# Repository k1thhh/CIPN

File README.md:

# 🩺 Chemo Comfort — AI-Based Wearable for Early Detection of CIPN

<p align="center">

**Embedded Healthcare | TinyML | ESP32 | Biomedical Sensing | Edge AI**

</p>

---

## 📌 Overview

**Chemo Comfort** is a portable, low-cost embedded diagnostic prototype designed for the **early, objective screening of Chemotherapy-Induced Peripheral Neuropathy (CIPN)**.

The system combines three complementary assessment methods:

* A simplified **EORTC QLQ-CIPN20 questionnaire**
* **Vibration Perception Threshold (VPT)** testing
* **Cold-temperature perception testing**

The extracted features are processed directly on an **ESP32-WROOM** using a quantized **TensorFlow Lite Micro neural network**, allowing the device to classify CIPN risk without relying on cloud connectivity.

The system produces one of three risk categories:

```text
Normal
Moderate
Severe
```

All processing is performed locally on the device, providing a privacy-preserving architecture suitable for potential home or outpatient applications.

> ⚠️ **Important:** Chemo Comfort is an academic/research prototype and is **not a certified medical device**. It is not intended for clinical diagnosis without further validation.

---

# 🩺 About Chemotherapy-Induced Peripheral Neuropathy

**Chemotherapy-Induced Peripheral Neuropathy (CIPN)** is a common adverse effect associated with several chemotherapy agents, including taxanes, platinum compounds, and vinca alkaloids.

Conventional assessment can involve:

* Patient-reported questionnaires
* Clinical grading scales
* Nerve conduction studies
* Quantitative sensory testing

The project aims to combine subjective patient-reported information with quantitative sensory measurements in a single portable embedded system.

---

# 🎯 Project Objectives

The primary objectives are:

1. Develop a portable embedded system for CIPN screening.
2. Collect patient-reported sensory, motor, and autonomic symptoms.
3. Measure vibration perception thresholds.
4. Measure cold-temperature perception.
5. Combine multiple sensory indicators into a unified feature vector.
6. Perform feature normalization directly on the ESP32.
7. Deploy a quantized TinyML model on-device.
8. Classify CIPN risk into Normal, Moderate, or Severe categories.
9. Display the classification locally using an OLED.
10. Eliminate the requirement for cloud-based inference.
11. Develop a low-cost prototype suitable for further research and validation.

---

# 🏗️ System Architecture

The system combines three input modules before performing edge inference.

```text id="4u9b3c"
┌─────────────────────┐
│   Questionnaire     │
│   OLED + Buttons    │
└──────────┬──────────┘
           │
           │
┌──────────▼──────────┐
│   Vibration Test    │
│    DRV2605L ×2      │
└──────────┬──────────┘
           │
           │
┌──────────▼──────────┐
│   Thermal Test      │
│ Peltier + Temp      │
│      Sensor         │
└──────────┬──────────┘
           │
           ▼
┌─────────────────────────┐
│       ESP32-WROOM       │
│                         │
│ Feature Normalization   │
│ Mean / Std Scaling      │
└────────────┬────────────┘
             │
             ▼
┌─────────────────────────┐
│   TFLite Micro Model    │
│     INT8 Quantized      │
│                         │
│ Dense(16, ReLU)         │
│        ↓                │
│ Dense(1, Sigmoid)       │
└────────────┬────────────┘
             │
             ▼
┌─────────────────────────┐
│      OLED Display       │
│ Normal / Moderate /     │
│ Severe                  │
└─────────────────────────┘
```

The five model features are:

```text id="e5q8kj"
VPT
Cold Temperature
CIPN20 Sensory
CIPN20 Motor
CIPN20 Autonomic
```

These features are normalized on-device using the same preprocessing parameters used during model development.

---

# 🔬 Assessment Modules

## 1️⃣ Questionnaire Module

The device presents a simplified **EORTC QLQ-CIPN20-based questionnaire** through the OLED display.

Five push buttons are used for interaction:

* Four questionnaire response buttons
* One reset/response button

The questionnaire contributes sensory, motor, and autonomic symptom features to the final model input.

---

# 2️⃣ Vibration Perception Threshold Test

The VPT test evaluates the user's ability to perceive controlled vibration stimuli.

The system uses **DRV2605L haptic drivers** to generate controlled vibration.

```text id="z3q1n0"
ESP32
  │
  ▼
DRV2605L
  │
  ▼
Increasing Vibration
  │
  ▼
Patient Perception
  │
  ▼
Button Response
  │
  ▼
VPT Threshold
```

The vibration intensity is progressively increased until the patient indicates that the vibration can be perceived.

The project reports VPT threshold trends of approximately:

```text id="kr9n5a"
Non-CIPN → Median 7–8
CIPN     → Median 17–18
```

---

# 3️⃣ Thermal Perception Test

The thermal test evaluates cold-temperature perception.

The system uses:

* TEC1-12706 Peltier module
* DS18B20 / TMP117 temperature sensor
* MOSFET H-bridge

The Peltier module changes the temperature of a contact surface while the temperature sensor continuously measures the resulting temperature.

```text id="n6l4yw"
ESP32
  │
  ▼
MOSFET H-Bridge
  │
  ▼
Peltier Module
  │
  ▼
Cooling Surface
  │
  ▼
Patient Perception
  │
  ▼
Cold Detection Threshold
```

The project reports cold-detection temperatures around:

```text id="d7b5ai"
30.0 – 30.7 °C
```

---

# 🧠 Feature Extraction

The three assessment modules produce the five model inputs:

| Feature            | Source                    |
| ------------------ | ------------------------- |
| `vpt`              | Vibration perception test |
| `cold_temp`        | Thermal perception test   |
| `cipn20_sensory`   | Questionnaire             |
| `cipn20_motor`     | Questionnaire             |
| `cipn20_autonomic` | Questionnaire             |

The complete feature vector is therefore:

```text id="j4bdl7"
[vpt,
 cold_temp,
 cipn20_sensory,
 cipn20_motor,
 cipn20_autonomic]
```

The preprocessing parameters are stored in:

```text id="4px0ck"
ml/model/preproc_params.json
```

and mirrored as constants in the firmware.

---

# 🤖 Machine Learning Pipeline

The machine-learning pipeline was developed using **Python, TensorFlow, and Google Colab**.

```text id="m2h52d"
Clinical / Synthetic Data
          │
          ▼
    Dataset Synthesis
          │
          ▼
     Preprocessing
          │
    ┌─────┴─────┐
    ▼           ▼
Imputation   Standardization
    │           │
    └─────┬─────┘
          ▼
       MLP Model
          │
          ▼
      Training
          │
          ▼
    TensorFlow Lite
          │
          ▼
     INT8 Quantization
          │
          ▼
       model.h
          │
          ▼
       ESP32
```

---

# 📊 Dataset Development

Because a public dataset combining quantitative sensory measurements with CIPN-20 scores was not available for the project's requirements, a **synthetic dataset** was generated.

The dataset was constructed using statistical patterns reported in published literature, with controlled mean and standard-deviation shifts between CIPN and non-CIPN classes.

This approach allowed the embedded ML pipeline to be developed and tested while recognizing that clinical validation with real patient data remains necessary.

---

# ⚙️ Data Preprocessing

The ML pipeline applies two major preprocessing operations.

## Median Imputation

Missing values are handled using:

```text id="u8scnd"
SimpleImputer
      ↓
Median Imputation
```

---

## Feature Standardization

The features are standardized using:

```text id="qzqu2m"
StandardScaler
```

The resulting mean and scaling parameters are saved in:

```text id="5w9f84"
preproc_params.json
```

The same preprocessing parameters are embedded into the ESP32 firmware to maintain consistency between training and inference.

---

# 🧠 Neural Network Architecture

The project uses a compact **two-layer Multilayer Perceptron (MLP)**.

```text id="3f53f5"
5 Input Features
       │
       ▼
┌──────────────────┐
│ Dense Layer      │
│ 16 Neurons       │
│ ReLU Activation  │
└────────┬─────────┘
         │
         ▼
┌──────────────────┐
│ Dense Layer      │
│ 1 Neuron         │
│ Sigmoid           │
└────────┬─────────┘
         │
         ▼
    CIPN Risk Score
```

The model was trained for:

```text id="4c3vqt"
Epochs      = 30
Optimizer   = Adam
Learning Rate = 0.001
Train/Test  = 85:15
```

---

# 📦 TensorFlow Lite Conversion

After training, the model is converted into an embedded-friendly representation.

```text id="m2trm8"
Keras Model
    ↓
TensorFlow Lite
    ↓
INT8 Post-Training Quantization
    ↓
C Array
    ↓
model.h
    ↓
ESP32 Firmware
```

The resulting `model.h` file contains the TensorFlow Lite model as a C byte array that can be compiled directly into the ESP32 firmware.

---

# ⚡ On-Device TinyML

One of the major features of Chemo Comfort is that inference occurs **directly on the ESP32**.

```text id="d0c4au"
Patient Data
     ↓
Feature Extraction
     ↓
Normalization
     ↓
INT8 TinyML Model
     ↓
Risk Classification
     ↓
OLED
```

No cloud server is required for inference.

This provides:

* Lower dependency on internet connectivity
* Local processing
* Improved privacy
* Potentially faster response
* Portable operation

The firmware executes the model using a **32 KB tensor arena**.

---

# 🖥️ OLED User Interface

A **0.96-inch 128×64 I²C OLED** provides the user interface.

It displays:

* Questionnaire prompts
* Progress
* Test information
* Final CIPN risk classification

The final classification is displayed as:

```text id="5qv8aq"
┌──────────────────┐
│   CIPN RESULT    │
│                  │
│     NORMAL       │
│       OR         │
│    MODERATE      │
│       OR         │
│     SEVERE       │
└──────────────────┘
```

---

# 💻 Firmware Architecture

The main firmware is:

```text id="3myq5u"
firmware/cipn_tinyml.ino
```

It integrates the complete embedded workflow.

The firmware handles:

* OLED interface
* Questionnaire flow
* Button debouncing
* VPT testing
* Thermal testing
* Feature normalization
* TinyML inference
* Risk classification
* Result display

---

# 🔌 Hardware Architecture

| Component              | Function                           |
| ---------------------- | ---------------------------------- |
| **ESP32-WROOM**        | Main controller + TinyML inference |
| **DRV2605L ×2**        | Vibration stimulus generation      |
| **TEC1-12706 Peltier** | Thermal stimulus                   |
| **DS18B20 / TMP117**   | Temperature sensing                |
| **MOSFET H-Bridge**    | Bidirectional Peltier control      |
| **MT3608**             | Boost conversion                   |
| **0.96" OLED**         | User interface                     |
| **5 Push Buttons**     | Questionnaire and test interaction |

The ESP32-WROOM uses a dual-core Xtensa LX6 architecture operating at up to 240 MHz with 520 KB SRAM.

---

# 💰 Cost Analysis

The prototype has an estimated total component cost of approximately:

## **₹1,710**

| Component          | Qty | Unit Cost |        Total |
| ------------------ | --: | --------: | -----------: |
| ESP32-WROOM        |   1 |      ₹400 |         ₹400 |
| DRV2605L           |   2 |      ₹180 |         ₹360 |
| Peltier Module     |   1 |      ₹200 |         ₹200 |
| DS18B20/TMP117     |   1 |      ₹120 |         ₹120 |
| MT3608             |   1 |       ₹80 |          ₹80 |
| OLED               |   1 |      ₹150 |         ₹150 |
| Push Buttons       |   5 |       ₹10 |          ₹50 |
| MOSFET H-Bridge    |   1 |      ₹100 |         ₹100 |
| Power Supply / USB |   1 |      ₹100 |         ₹100 |
| Miscellaneous      |   — |         — |         ₹150 |
| **Total**          |     |           | **≈ ₹1,710** |

---

# 📁 Repository Structure

```text id="y5x4b9"
ChemoComfort-CIPN-Wearable/
│
├── README.md
│
├── docs/
│   └── Chemo_Comfort_Project_Report.pdf
│
├── firmware/
│   ├── cipn_tinyml.ino
│   └── model.h
│
├── ml/
│   ├── notebooks/
│   │   └── cipn.ipynb
│   │
│   ├── data/
│   │   ├── cipn_cancer_drug_only.csv
│   │   └── taxane.csv
│   │
│   └── model/
│       └── preproc_params.json
│
└── PCB/
    ├── esd_pcb_design.kicad_pro
    ├── esd_pcb_design.kicad_sch
    ├── esd_pcb_design.kicad_pcb
    └── esd_pcb_design.kicad_prl
```

The repository therefore combines **embedded firmware, TinyML training artifacts, datasets, preprocessing parameters, and PCB design files** in a single project structure.

---

# 🛠️ Tools & Technologies

## Embedded

* ESP32-WROOM
* Arduino IDE
* Embedded C/C++
* I²C
* GPIO
* PWM
* Sensor interfacing

## Machine Learning

* Python
* TensorFlow
* TensorFlow Lite
* TensorFlow Lite Micro
* Google Colab
* INT8 quantization

## Hardware Design

* KiCad
* PCB schematic design
* PCB layout

## User Interface

* OLED
* Push buttons
* Serial Monitor

---

# 📚 Required Arduino Libraries

The firmware uses:

```text id="c1ytp2"
Adafruit_GFX
Adafruit_SSD1306
Adafruit_DRV2605
tflm_esp32
eloquent_tinyml
Wire
```

`Wire` is included with the Arduino/ESP32 environment.

---

# 🚀 Getting Started

## 1️⃣ Machine Learning Pipeline

Open:

```text id="j9g2xh"
ml/notebooks/cipn.ipynb
```

using Google Colab or Jupyter.

The notebook contains the dataset synthesis, preprocessing, model training, and TensorFlow Lite conversion workflow.

---

## 2️⃣ PCB Design

The PCB design can be opened using **KiCad 8.x or later**.

The main project file is:

```text id="v1p9cq"
PCB/esd_pcb_design.kicad_pro
```

The repository also contains the schematic and PCB layout files.

---

## 3️⃣ Flash the ESP32

Open:

```text id="q1fs93"
firmware/cipn_tinyml.ino
```

Ensure that:

```text id="8l72t4"
model.h
```

is present in the same sketch directory.

Install the required Arduino libraries, select the appropriate ESP32 board and COM port, then upload the firmware.

---

# 🔄 Complete System Workflow

```text id="5a6m2e"
             START
               │
               ▼
        Questionnaire
               │
               ▼
        Sensory Scores
               │
               ▼
        VPT Measurement
               │
               ▼
       Vibration Threshold
               │
               ▼
      Thermal Measurement
               │
               ▼
      Cold Detection Temp
               │
               ▼
      ┌──────────────────┐
      │ 5 Feature Vector │
      └────────┬─────────┘
               │
               ▼
       Median Imputation
               │
               ▼
      Standardized Features
               │
               ▼
       INT8 TinyML Model
               │
               ▼
      CIPN Risk Classification
               │
        ┌──────┼──────┐
        ▼      ▼      ▼
      Normal Moderate Severe
               │
               ▼
             OLED
```

---

# 📊 Project Results

The implemented prototype demonstrates:

| Parameter                     | Result                                |
| ----------------------------- | ------------------------------------- |
| Architecture                  | ESP32-based edge diagnostic prototype |
| Input Modalities              | Questionnaire + VPT + thermal         |
| ML Model                      | 2-layer MLP                           |
| Model Quantization            | INT8                                  |
| Input Features                | 5                                     |
| Tensor Arena                  | 32 KB                                 |
| Inference Time                | **< 1 second**                        |
| Reported AUC                  | **≈ 0.70–0.90**                       |
| PC-to-device parity deviation | **< 2%**                              |
| Estimated Cost                | **≈ ₹1,710**                          |

The reported AUC varies between training runs, while the project reports less than 2% parity deviation from the PC-based Keras model and consistently sub-second ESP32 inference.

---

# 🔍 Verification Strategy

The system can be evaluated at multiple levels.

### Hardware Verification

Verify:

* Vibration generation
* Temperature measurement
* Peltier control
* OLED operation
* Button response

### Sensor Verification

Compare VPT and thermal measurements with expected trends.

### ML Verification

Compare the embedded model's output against the original PC-based Keras model.

### Quantization Verification

Evaluate whether INT8 conversion significantly changes model predictions.

### Embedded Performance

Measure:

* Inference latency
* Memory usage
* Tensor arena requirements
* End-to-end test duration

### System-Level Verification

Verify that questionnaire responses, sensory measurements, preprocessing, inference, and OLED output work as one integrated system.

---

# 🧠 Key Concepts Demonstrated

This project provides practical exposure to:

* Embedded healthcare systems
* Biomedical sensing
* CIPN screening
* ESP32 development
* TinyML
* Edge AI
* TensorFlow Lite Micro
* INT8 quantization
* Neural-network deployment
* Feature normalization
* Median imputation
* Vibration perception testing
* Thermal perception testing
* Peltier control
* Temperature sensing
* Haptic feedback
* OLED interfaces
* Embedded machine learning
* PCB design
* KiCad
* Hardware-software integration

---

# 💡 What I Learned

The project demonstrates how a machine-learning model can move from a Python training environment into a resource-constrained embedded device.

The complete development pipeline can be summarized as:

```text id="qf8qgl"
Data
  ↓
Preprocessing
  ↓
Model Training
  ↓
TensorFlow Lite
  ↓
INT8 Quantization
  ↓
C Array Conversion
  ↓
ESP32 Deployment
  ↓
On-Device Inference
  ↓
Risk Classification
```

At the same time, the project combines **physical sensing, embedded firmware, PCB design, and machine learning** into one end-to-end system.

This makes the project an example of how TinyML can be used to move AI inference closer to the point of data acquisition.

---

# 🏥 Potential Applications

The underlying architecture could potentially be extended to:

### Home Screening

Portable preliminary monitoring outside a hospital environment.

### Outpatient Monitoring

Repeated measurements during chemotherapy treatment.

### Telemedicine

Future wireless connectivity could allow measurements to be shared with healthcare providers.

### Rehabilitation

The same sensory-measurement architecture could potentially be adapted for monitoring changes in peripheral sensory function over time.

> These are potential applications of the prototype; clinical suitability would require substantial real-world validation and regulatory evaluation.

---

# ⚠️ Limitations

The current prototype has several important limitations.

### Synthetic Training Data

The ML dataset was synthesized because a suitable public dataset combining the required sensory measurements and CIPN-20 scores was unavailable.

### Clinical Validation

The model requires validation using real patient data before any clinical interpretation.

### Model Performance

The reported AUC ranges from approximately **0.70–0.90 depending on the training run**, so performance is not yet sufficient to establish clinical reliability.

### Hardware Resolution

The current thermal and vibration measurement mechanisms provide prototype-level sensory measurements rather than certified clinical measurements.

### Regulatory Status

## The system is an academic/research prototype and is **not a certified medical device**.

# 🚀 Future Scope

The project can be extended through:

* Collection of real patient data
* Clinical retraining and validation
* Larger and more diverse datasets
* Electrodermal activity sensing
* Tactile-response timing measurements
* Bluetooth connectivity
* Wi-Fi connectivity
* Telemonitoring
* EHR integration
* Closed-loop PID thermal control
* Higher-resolution temperature threshold measurement
* Touchscreen interface
* Companion mobile application
* Li-ion battery operation
* Portable enclosure
* Medical-device compliance pathway

These extensions are consistent with the project's documented future-work directions.

---

# 📈 Future System Architecture

A future version could evolve toward:

```text id="ynp5i3"
        Multi-Modal Sensing
               │
       ┌───────┼────────┐
       ▼       ▼        ▼
      VPT    Thermal  Questionnaire
       │       │        │
       └───────┼────────┘
               ▼
        Feature Fusion
               │
               ▼
       Edge AI / TinyML
               │
               ▼
       Risk Estimation
               │
       ┌───────┴────────┐
       ▼                ▼
 Local OLED       Wireless Report
                         │
                         ▼
                   Telemonitoring
```

---

# ⭐ Project Highlights

* 🔹 **AI-based CIPN screening prototype**
* 🔹 Multi-modal sensory assessment
* 🔹 EORTC QLQ-CIPN20-based questionnaire
* 🔹 Vibration Perception Threshold testing
* 🔹 Peltier-based thermal perception testing
* 🔹 ESP32-WROOM embedded platform
* 🔹 **On-device TinyML inference**
* 🔹 TensorFlow Lite Micro
* 🔹 **INT8 model quantization**
* 🔹 5-feature ML input vector
* 🔹 2-layer MLP architecture
* 🔹 Sub-second inference
* 🔹 PC-to-device parity within **<2%**
* 🔹 OLED-based user interface
* 🔹 Custom PCB design using KiCad
* 🔹 Estimated prototype cost of **~₹1,710**
* 🔹 Completely offline inference
* 🔹 Privacy-preserving edge architecture

---

# 👥 Authors

**Kirthana S**
**R. Gopikasree**
**Joshitha G**

**Guide:** Dr. V. Prakash

**School of Electronics Engineering**
**Vellore Institute of Technology, Chennai**

The project was developed as part of **BECE403E – Embedded System Design (November 2025)**.

---

# 📌 Keywords

`CIPN` `Chemotherapy-Induced Peripheral Neuropathy` `TinyML` `Edge AI` `ESP32` `TensorFlow Lite` `TensorFlow Lite Micro` `Biomedical Engineering` `Embedded Systems` `Healthcare AI` `Vibration Perception` `Thermal Perception` `Peltier` `DRV2605L` `OLED` `Machine Learning` `INT8 Quantization` `CIPN20` `EORTC` `KiCad` `PCB Design` `Embedded ML` `On-Device Inference`

---

<p align="center">

**Sense → Extract → Normalize → Infer → Classify**

</p>

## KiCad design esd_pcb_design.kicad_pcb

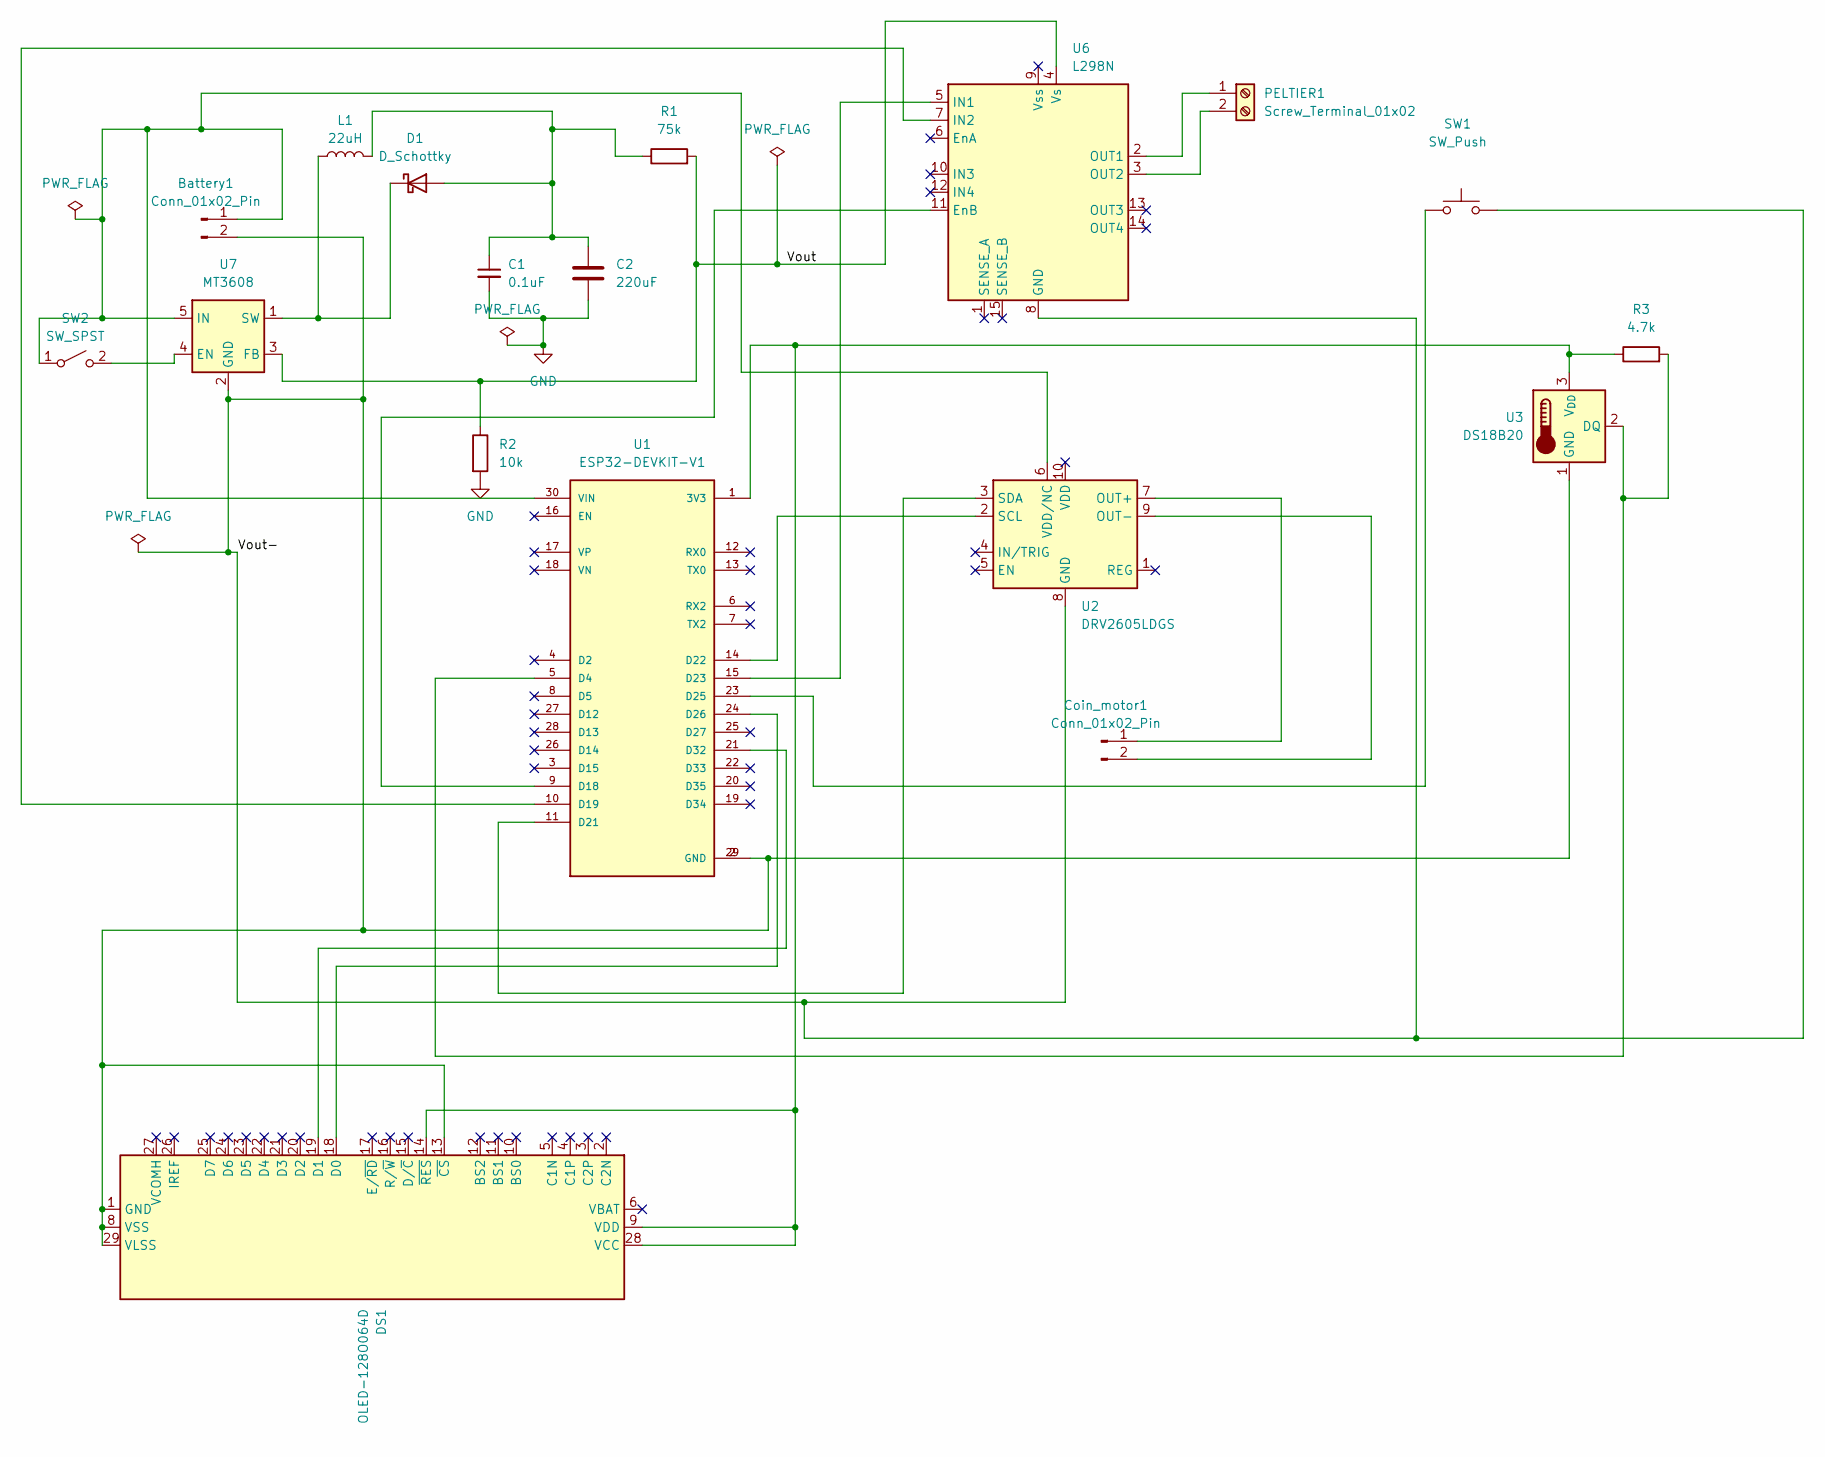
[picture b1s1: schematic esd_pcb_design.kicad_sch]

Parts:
Battery1: Conn_01x02_Pin; JST_PH_S2B-PH-K_1x02_P2.00mm_Horizontal
C1: 0.1uF; C_Disc_D5.0mm_W2.5mm_P2.50mm
C2: 220uF; CP_Radial_D6.3mm_P2.50mm
Coin_motor1: Conn_01x02_Pin; PinHeader_1x02_P2.54mm_Vertical
D1: D_Schottky; D_DO-41_SOD81_P10.16mm_Horizontal
DS1: OLED-128O064D
L1: 22uH; L_Axial_L6.6mm_D2.7mm_P2.54mm_Vertical_Vishay_IM-2
PELTIER1: Screw_Terminal_01x02; TerminalBlock_Phoenix_MKDS-1,5-2-5.08_1x02_P5.08mm_Horizont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
R1: 75k; R_Axial_DIN0207_L6.3mm_D2.5mm_P10.16mm_Horizontal
R2: 10k; R_Axial_DIN0207_L6.3mm_D2.5mm_P10.16mm_Horizontal
R3: 4.7k; R_Axial_DIN0207_L6.3mm_D2.5mm_P10.16mm_Horizontal
SW1: SW_Push; SW_PUSH_6mm
SW2: SW_SPST; PinHeader_1x02_P2.54mm_Vertical_SMD_Pin1Left
U1: ESP32-DEVKIT-V1; MODULE_ESP32_DEVKIT_V1; PARTREV N/A
U2: DRV2605LDGS; VSSOP-10_3x3mm_P0.5mm
U3: DS18B20; TO-92_Inline
U6: L298N; TO-220-15_P2.54x5.08mm_StaggerOdd_Lead4.58mm_Vertical
U7: MT3608; SOT-23-6

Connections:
/Vout: R1.2, R2.1, U6.4 (Vs), U7.3 (FB)
/Vout-: Battery1.2, DS1.1 (GND), DS1.8 (VSS), DS1.13 (~CS), DS1.29 (VLSS), DS1.30 (GND), SW1.2, U1.2 (GND), U1.29 (GND), U2.8 (GND), U3.1 (GND), U6.8 (GND), U7.2 (GND)
GND: C1.2, C2.2, R2.2
unnamed: Battery1.1, SW2.1 (A), U1.30 (VIN), U2.6 (VDD/NC), U7.5 (IN)
unnamed: Coin_motor1.1, U2.7 (OUT+)
unnamed: Coin_motor1.2, U2.9 (OUT-)
unnamed: C1.1, C2.1, D1.2 (A), L1.2, R1.1
unnamed: D1.1 (K), L1.1, U7.1 (SW)
unnamed: DS1.18 (D0), U1.24 (D26)
unnamed: DS1.19 (D1), U1.21 (D32)
unnamed: DS1.9 (VDD), DS1.14 (~RES), DS1.28 (VCC), R3.1, U1.1 (3V3), U3.3 (V_{DD})
unnamed: PELTIER1.1, U6.2 (OUT1)
unnamed: PELTIER1.2, U6.3 (OUT2)
unnamed: SW2.2 (B), U7.4 (EN)
unnamed: R3.2, U1.5 (D4), U3.2 (DQ)
unnamed: U1.9 (D18), U6.11 (EnB)
unnamed: U1.10 (D19), U6.7 (IN2)
unnamed: U1.11 (D21), U2.3 (SDA)
unnamed: U1.14 (D22), U2.2 (SCL)
unnamed: U1.15 (D23), U6.5 (IN1)
unnamed: SW1.1, U1.23 (D25)

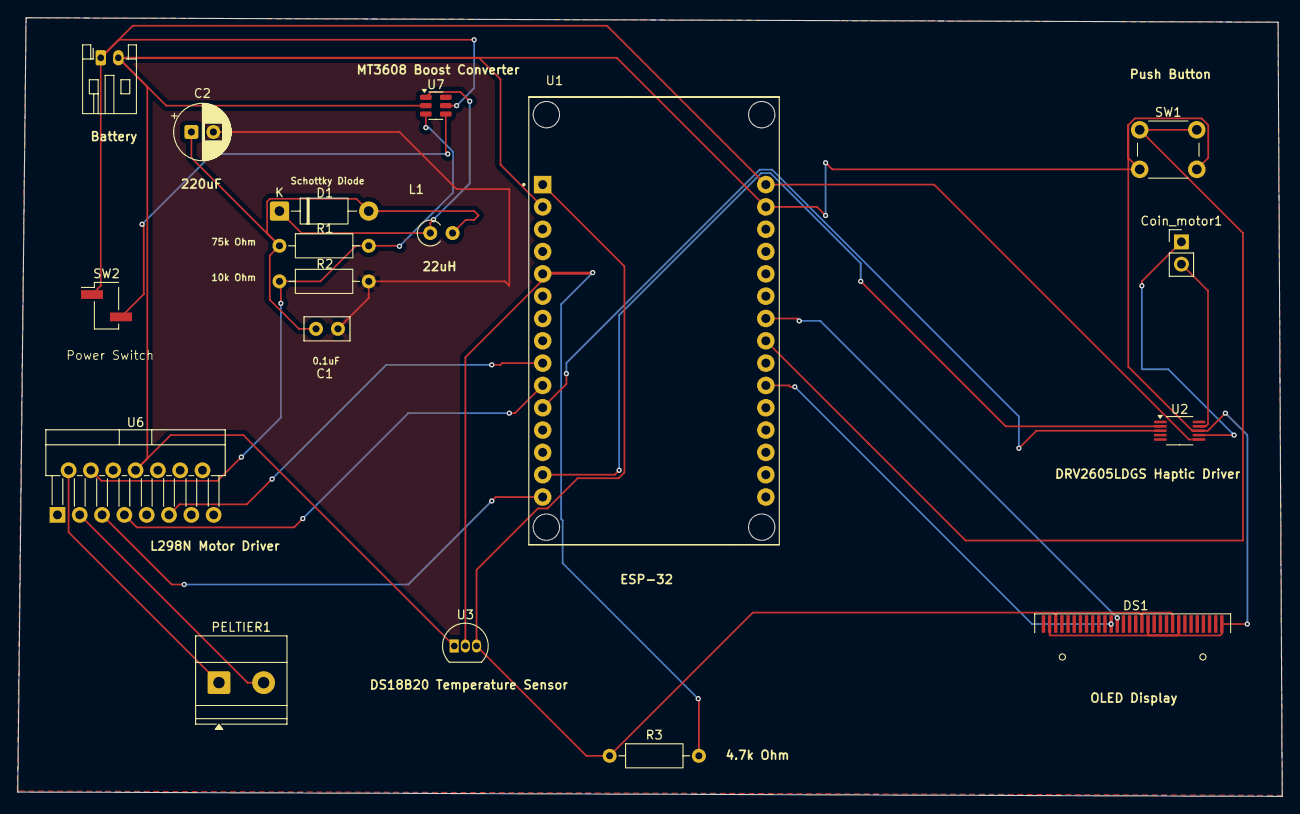
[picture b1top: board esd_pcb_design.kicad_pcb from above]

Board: 2 copper layers, 143.9 x 88.6 mm, 18 parts (0 on the bottom side), 21 nets.
